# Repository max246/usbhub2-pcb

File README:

# USBHUB version 2 PCB

I have made a preview one with another chip, which ended up to be too complicated for my purpose, it worked but this has less components to solder.
This version has 2 mosfet which needs to be connected to a pin 5V or just removed from the schematic. It was for my personal project but no needed if you need a normal usb hub.

The schematic was inspired by: https://github.com/richardhawthorn/piZero-Hub

I used SI2301CDS-T1-E3  as Mosfet to make sure there can handle enough Ampere.

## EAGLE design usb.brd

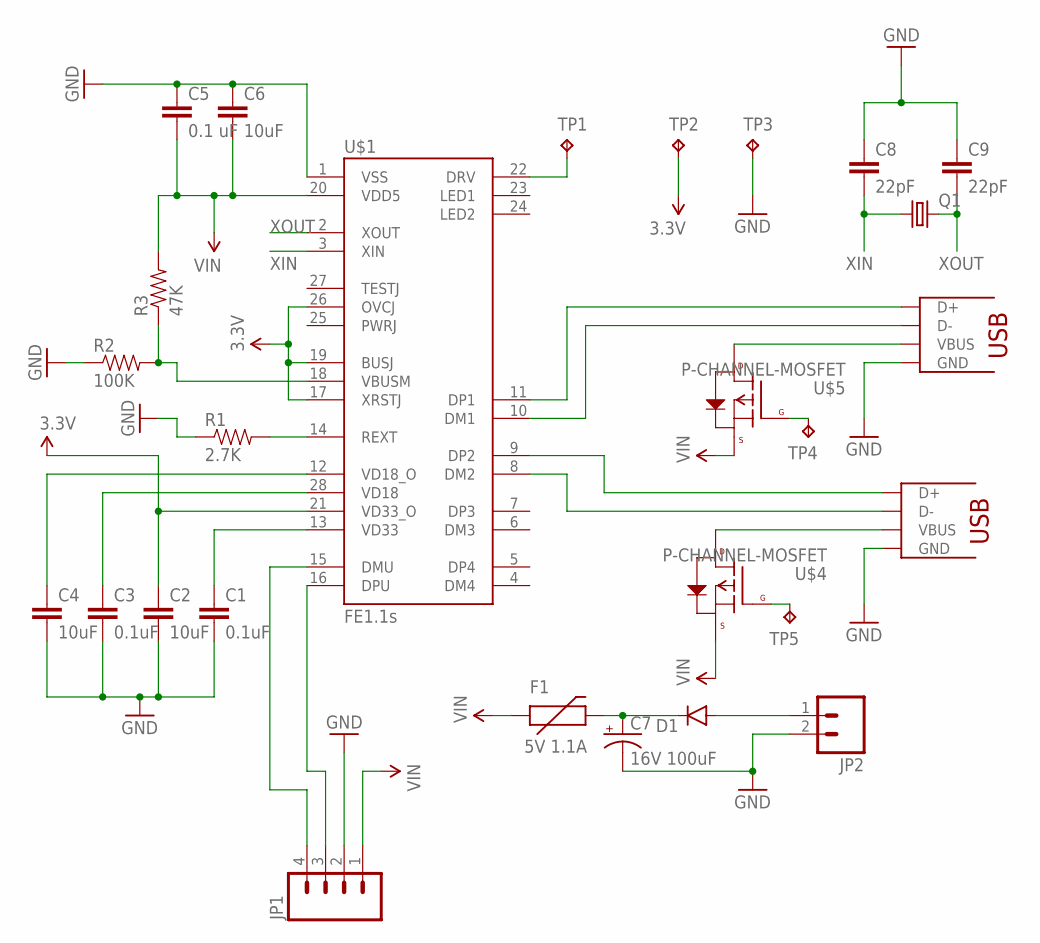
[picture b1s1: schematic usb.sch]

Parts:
C1, C3: 0.1uF; 1206; MPN CGA5L2C0G1H104J160AA
C2, C4, C6: 10uF; 1206; MPN GMK316F106ZL-T
C5: 0.1 uF; 1206; MPN CGA5L2C0G1H104J160AA
C7: 16V 100uF; PANASONIC_D; MPN EEEHA1C101WP
C8, C9: 22pF; 1206; MPN 12061A220JAT2A
D1: DIODESMA; SMA-DIODE; MPN SMAJ5.0A
F1: 5V 1.1A; PTC-1206
JP1: M04LONGPADS; 1X04_LONGPADS
JP2: M02PTH; 1X02
Q1: CRYSTALCTS406; CTS406; MPN ABM3B-12.000MHZ-B2-T
R1: 2.7K; 1206; MPN WCR1206-2K7FI
R2: 100K; 1206; MPN CRCW1206100KFKEA
R3: 47K; 1206; MPN CRCW120647K0FKEA
TP1, TP2, TP3, TP4, TP5: TP_DRV; B2,54
U$1: FE1.1S; FE1.1S_SSOP-28
U$2, U$3: USB-A-S; USB-A-S-RA-PTH
U$4, U$5: P-CHANNEL-MOSFET; SOT23-3; MPN SI2301CDS-T1-E3

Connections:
3.3V: C2.1, TP2.TP, U$1.17 (XRSTJ), U$1.19 (BUSJ), U$1.21 (VD33_O), U$1.26 (OVCJ)
GND: C1.2, C2.2, C3.2, C4.2, C5.1, C6.1, C7.-, C8.1, C9.1, JP1.2, JP2.2, R1.1, R2.1, TP3.TP, U$1.1 (VSS), U$2.GND, U$2.GND2 (GND), U$2.GND3 (GND), U$3.GND, U$3.GND2 (GND), U$3.GND3 (GND)
unnamed: C1.1, U$1.13 (VD33)
unnamed: TP1.TP, U$1.22 (DRV)
unnamed: C3.1, U$1.28 (VD18)
unnamed: C4.1, U$1.12 (VD18_O)
unnamed: D1.A, JP2.1
unnamed: C7.+, D1.C, F1.2
unnamed: R1.2, U$1.14 (REXT)
unnamed: U$3.VBUS, U$4.3 (D)
unnamed: R2.2, R3.1, U$1.18 (VBUSM)
unnamed: U$2.VBUS, U$5.3 (D)
unnamed: TP5.TP, U$4.1 (G)
unnamed: TP4.TP, U$5.1 (G)
USB1_N: U$1.10 (DM1), U$2.D-
USB1_P: U$1.11 (DP1), U$2.D+
USB2_N: U$1.8 (DM2), U$3.D-
USB2_P: U$1.9 (DP2), U$3.D+
USBIN_N: JP1.4, U$1.15 (DMU)
USBIN_P: JP1.3, U$1.16 (DPU)
VIN: C5.2, C6.2, F1.1, JP1.1, R3.2, U$1.20 (VDD5), U$4.2 (S), U$5.2 (S)
XIN: C8.2, Q1.1, U$1.3 (XIN)
XOUT: C9.2, Q1.3 (2), U$1.2 (XOUT)

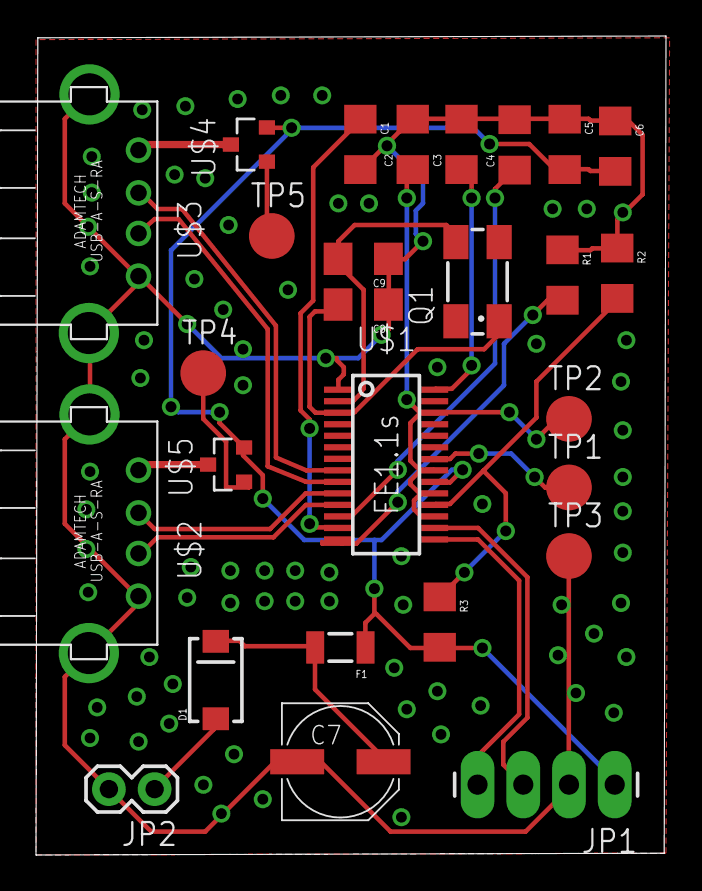
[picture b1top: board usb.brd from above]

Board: 2 copper layers, 35.0 x 45.5 mm, 27 parts (0 on the bottom side), 23 nets.

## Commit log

2016-11-26 add files
2016-11-26 Rename README to README.md

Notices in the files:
parts and their libraries:
SparkFun-Capacitors: Licensing: Creative Commons ShareAlike 4.0 International - https://creativecommons.org/licenses/by-sa/4.0
pimoroni: Licensing: CC v3.0 Share-Alike You are welcome to use this library for commercial purposes.
